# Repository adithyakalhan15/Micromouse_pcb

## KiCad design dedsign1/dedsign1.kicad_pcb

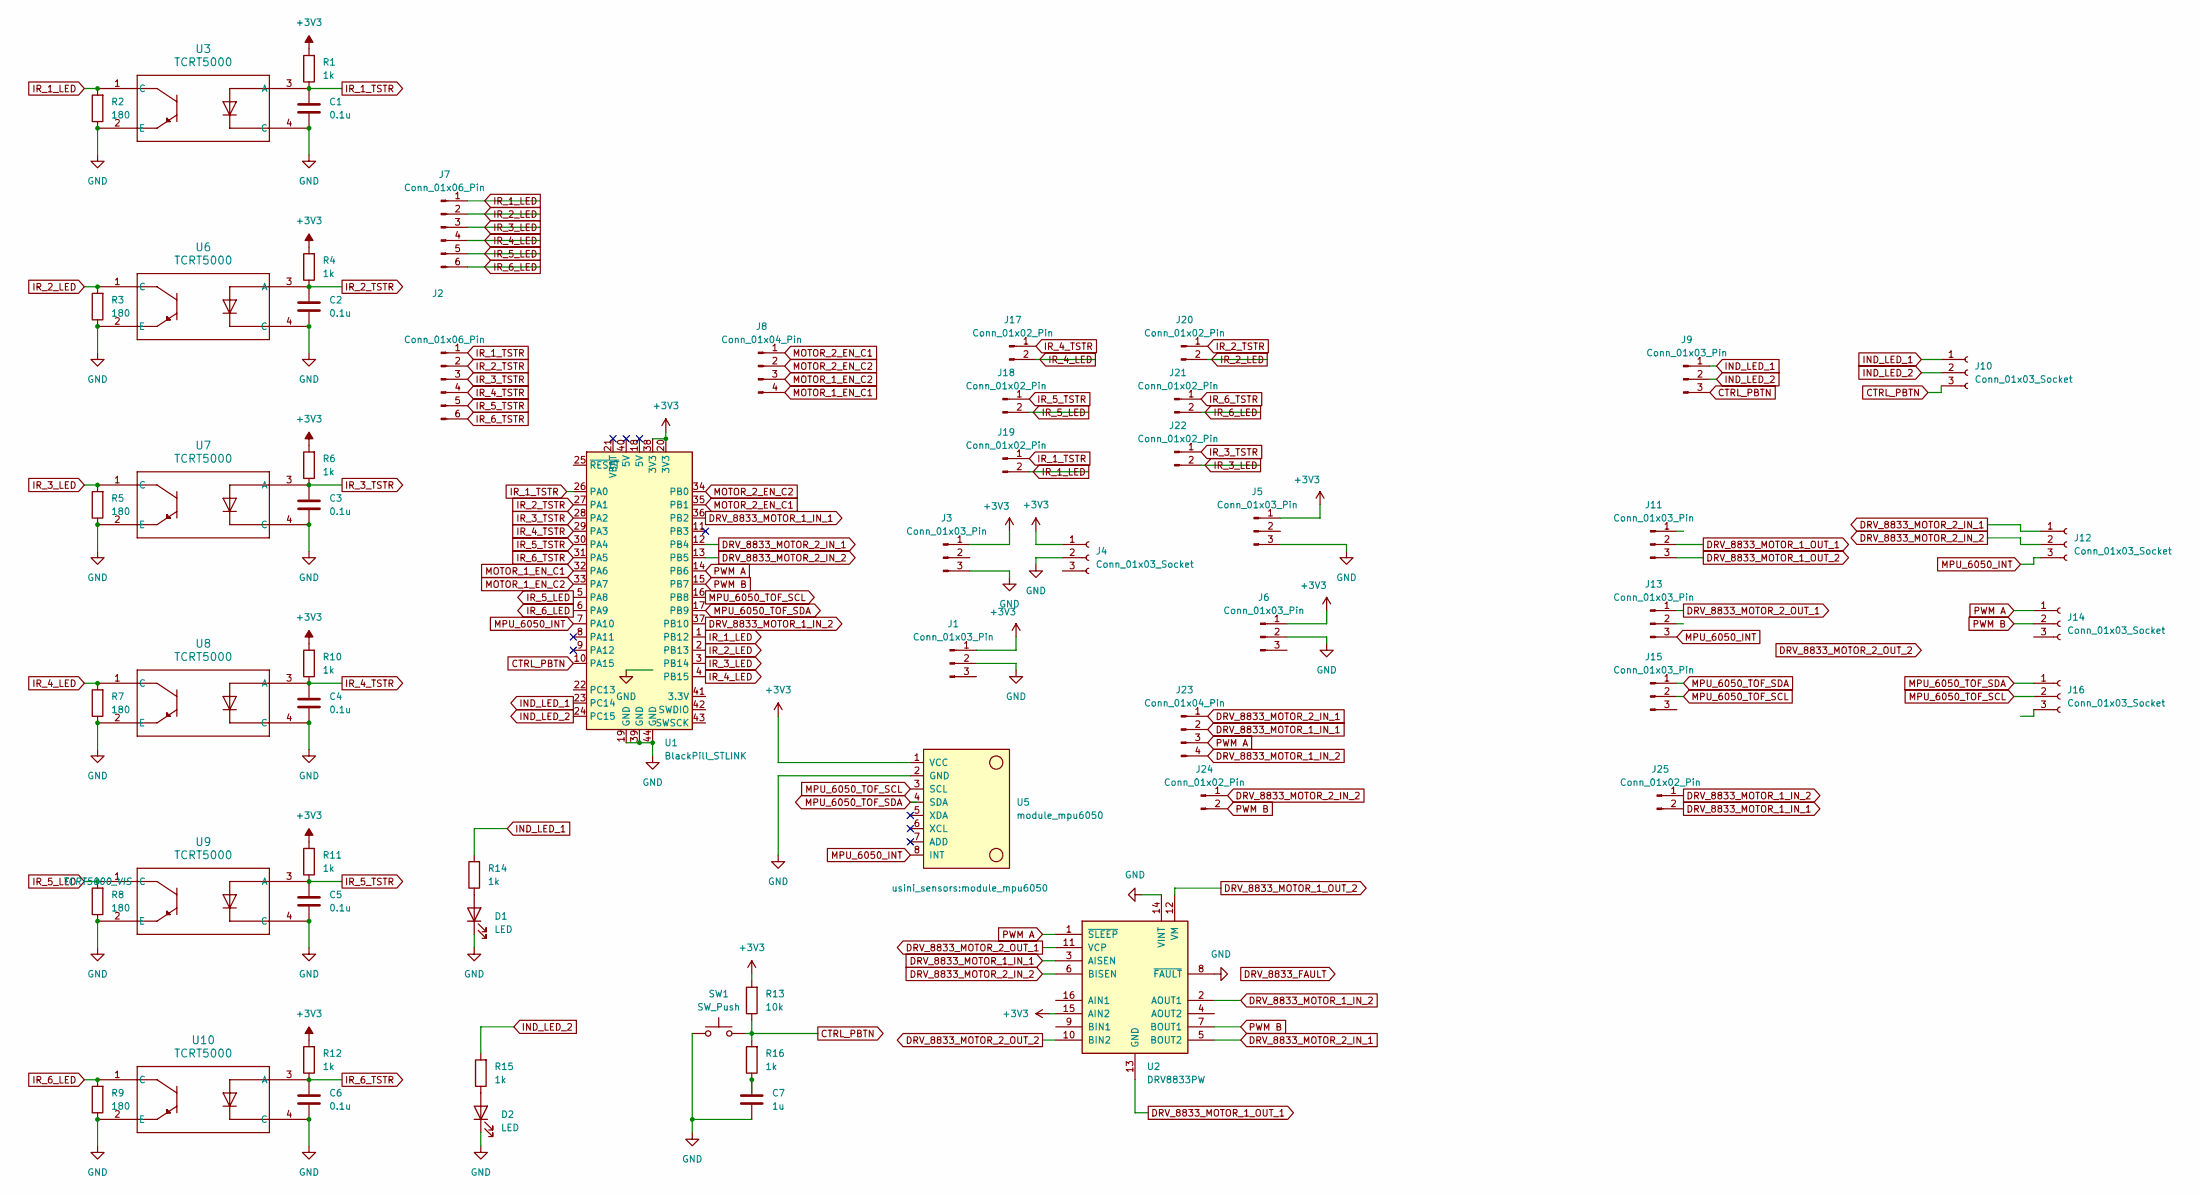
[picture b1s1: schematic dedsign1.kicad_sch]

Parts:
C1, C2, C3, C4, C5, C6: 0.1u; C_Disc_D4.3mm_W1.9mm_P5.00mm
C7: 1u; CP_Radial_D5.0mm_P2.50mm
D1, D2: LED; LED_D3.0mm_FlatTop
J1, J3, J5, J6, J9, J11, J13, J15: Conn_01x03_Pin; PinSocket_1x03_P1.27mm_Vertical
J2, J7: Conn_01x06_Pin; PinSocket_1x06_P1.00mm_Vertical
J4, J10, J12, J14, J16: Conn_01x03_Socket; PinSocket_1x03_P1.27mm_Vertical
J8, J23: Conn_01x04_Pin; PinSocket_1x04_P1.27mm_Vertical
J17, J18, J19, J20, J21, J22, J24, J25: Conn_01x02_Pin; PinHeader_1x02_P2.00mm_Vertical
R1, R4, R6, R10, R11, R12, R14, R15, R16: 1k; R_Axial_DIN0309_L9.0mm_D3.2mm_P12.70mm_Horizontal
R2, R3, R5, R7, R8, R9: 180; R_Axial_DIN0309_L9.0mm_D3.2mm_P12.70mm_Horizontal
R13: 10k; R_Axial_DIN0309_L9.0mm_D3.2mm_P12.70mm_Horizontal
SW1: SW_Push; SW_PUSH_6mm
U1: BlackPill_STLINK
U2: DRV8833PW; TSSOP-16_4.4x5mm_P0.65mm
U3, U6, U7, U8, U9, U10: TCRT5000; TCRT5000_VIS
U5: module_mpu6050

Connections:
+3V3: J1.1, J3.1, J4.1, J5.1, J6.1, R1.2, R4.2, R6.2, R10.2, R11.2, R12.2, R13.2, U1.20 (3V3), U1.38 (3V3), U2.15 (AIN2), U5.1 (VCC)
CTRL_PBTN: J9.3, J10.3, R13.1, R16.2, SW1.2, U1.10 (PA15)
DRV_8833_MOTOR_1_IN_1: J23.2, J25.2, U1.36 (PB2), U2.3 (AISEN)
DRV_8833_MOTOR_1_IN_2: J23.4, J25.1, U1.37 (PB10), U2.2 (AOUT1)
DRV_8833_MOTOR_1_OUT_1: J11.2, U2.13 (GND)
DRV_8833_MOTOR_1_OUT_2: J11.3, U2.12 (VM)
DRV_8833_MOTOR_2_IN_1: J12.1, J23.1, U1.12 (PB4), U2.5 (BOUT2)
DRV_8833_MOTOR_2_IN_2: J12.2, J24.1, U1.13 (PB5), U2.6 (BISEN)
DRV_8833_MOTOR_2_OUT_1: J13.1, U2.11 (VCP)
DRV_8833_MOTOR_2_OUT_2: U2.10 (BIN2)
GND: C1.2, C2.2, C3.2, C4.2, C5.2, C6.2, C7.2, D1.1 (K), D2.1 (K), J1.2, J3.3, J4.2, J5.3, J6.2, R2.1, R3.1, R5.1, R7.1, R8.1, R9.1, SW1.1, U1.19 (GND), U1.39 (GND), U1.44 (GND), U2.8 (~FAULT), U2.14 (VINT), U3.2 (E), U3.4 (C), U5.2 (GND), U6.2 (E), U6.4 (C), U7.2 (E), U7.4 (C), U8.2 (E), U8.4 (C), U9.2 (E), U9.4 (C), U10.2 (E), U10.4 (C)
IND_LED_1: J9.1, J10.1, R14.2, U1.23 (PC14)
IND_LED_2: J9.2, J10.2, R15.2, U1.24 (PC15)
IR_1_LED: J7.1, J19.2, R2.2, U1.1 (PB12), U3.1 (C)
IR_1_TSTR: C1.1, J2.1, J19.1, R1.1, U1.26 (PA0), U3.3 (A)
IR_2_LED: J7.2, J20.2, R3.2, U1.2 (PB13), U6.1 (C)
IR_2_TSTR: C2.1, J2.2, J20.1, R4.1, U1.27 (PA1), U6.3 (A)
IR_3_LED: J7.3, J22.2, R5.2, U1.3 (PB14), U7.1 (C)
IR_3_TSTR: C3.1, J2.3, J22.1, R6.1, U1.28 (PA2), U7.3 (A)
IR_4_LED: J7.4, J17.2, R7.2, U1.4 (PB15), U8.1 (C)
IR_4_TSTR: C4.1, J2.4, J17.1, R10.1, U1.29 (PA3), U8.3 (A)
IR_5_LED: J7.5, J18.2, R8.2, U1.5 (PA8), U9.1 (C)
IR_5_TSTR: C5.1, J2.5, J18.1, R11.1, U1.30 (PA4), U9.3 (A)
IR_6_LED: J7.6, J21.2, R9.2, U1.6 (PA9), U10.1 (C)
IR_6_TSTR: C6.1, J2.6, J21.1, R12.1, U1.31 (PA5), U10.3 (A)
MOTOR_1_EN_C1: J8.4, U1.32 (PA6)
MOTOR_1_EN_C2: J8.3, U1.33 (PA7)
MOTOR_2_EN_C1: J8.1, U1.35 (PB1)
MOTOR_2_EN_C2: J8.2, U1.34 (PB0)
MPU_6050_INT: J12.3, J13.3, U1.7 (PA10), U5.8 (INT)
MPU_6050_TOF_SCL: J15.2, J16.2, U1.16 (PB8), U5.3 (SCL)
MPU_6050_TOF_SDA: J15.1, J16.1, U1.17 (PB9), U5.4 (SDA)
unnamed: C7.1, R16.1
unnamed: D1.2 (A), R14.1
unnamed: D2.2 (A), R15.1
PWM A: J14.1, J23.3, U1.14 (PB6), U2.1 (~SLEEP)
PWM B: J14.2, J24.2, U1.15 (PB7), U2.7 (BOUT1)

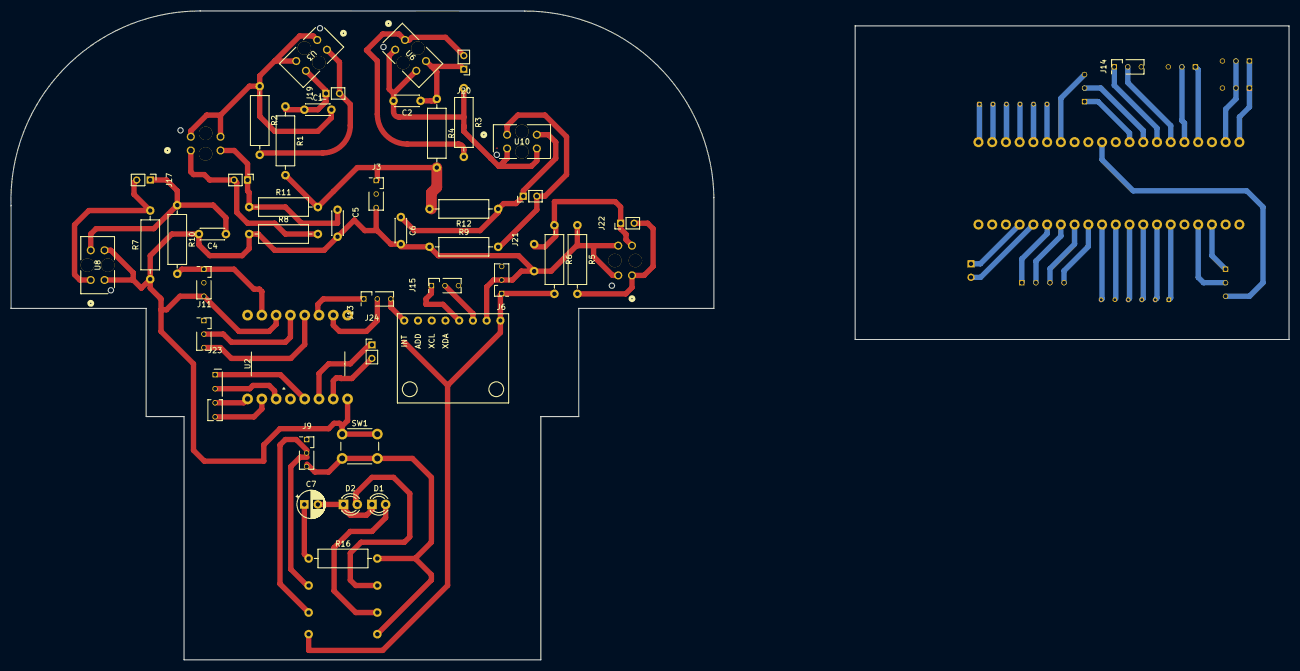
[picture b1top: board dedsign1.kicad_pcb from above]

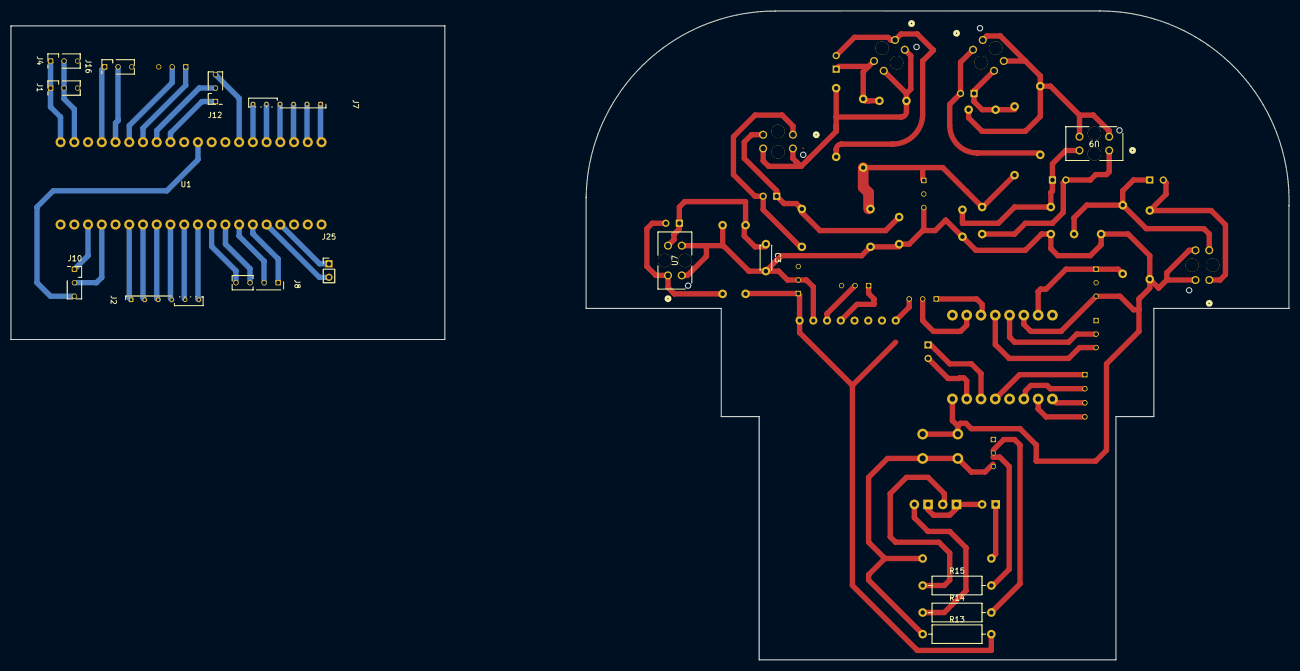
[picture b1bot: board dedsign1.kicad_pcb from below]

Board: 2 copper layers, 130.0 x 120.0 mm, 60 parts (16 on the bottom side), 36 nets.
